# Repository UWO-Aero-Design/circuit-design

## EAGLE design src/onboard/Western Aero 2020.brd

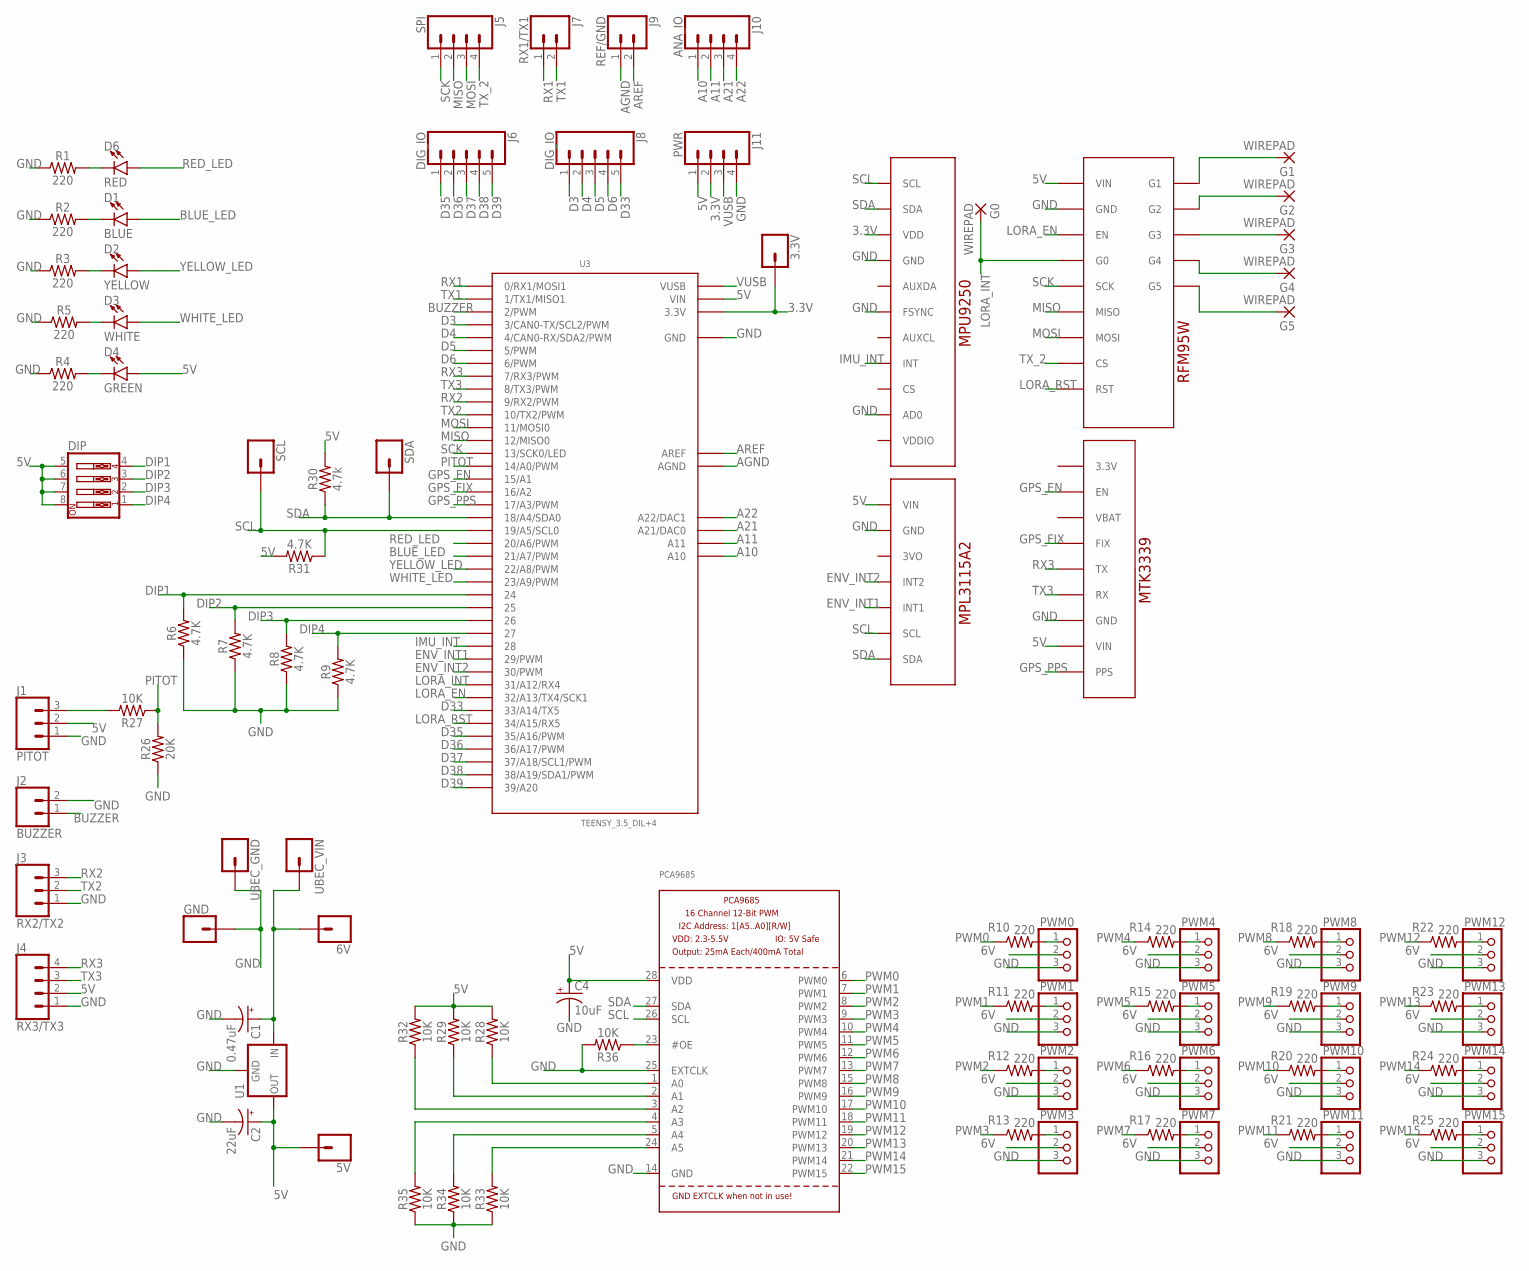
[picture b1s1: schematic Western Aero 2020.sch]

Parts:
3.3V, 5V, 6V: CONN_01; 1X01
C1: 0.47uF; CPOL-RADIAL-2.5MM-5MM
C2: 22uF; CPOL-RADIAL-2.5MM-5MM
C4: 10uF; CPOL-RADIAL-2.5MM-5MM
D1: BLUE; LED_5MM
D2: YELLOW; LED_5MM
D3: WHITE; LED_5MM
D4: GREEN; LED_5MM
D6: RED; LED_5MM
DIP: SW_DIP-4; EDG-04
G0, G1, G2, G3, G4, G5: WIREPAD; 2,15/1,0
GND: CONN_01; 1X01
J1: PITOT; 1X03
J2: BUZZER; 1X02
J3: RX2/TX2; 1X03
J4: RX3/TX3; 1X04
J5: SPI; 1X04
J6, J8: DIG_IO; 1X05
J7: RX1/TX1; 1X02
J9: REF/GND; 1X02
J10: ANA_IO; 1X04
J11: PWR; 1X04
JP1: PWM0; 1X03
JP2: PWM1; 1X03
JP3: PWM2; 1X03
JP4: PWM3; 1X03
JP5: PWM4; 1X03
JP6: PWM5; 1X03
JP7: PWM6; 1X03
JP8: PWM7; 1X03
JP9: PWM8; 1X03
JP10: PWM9; 1X03
JP11: PWM10; 1X03
JP12: PWM11; 1X03
JP13: PWM12; 1X03
JP14: PWM13; 1X03
JP15: PWM14; 1X03
JP16: PWM15; 1X03
PCA9685: PCA9685; TSSOP28
R1, R2, R3, R4, R5, R10, R11, R12, R13, R14, R15, R16, R17, R18, R19, R20, R21, R22, R23, R24, R25: 220; AXIAL-0.3
R6, R7, R8, R9, R31: 4.7K; AXIAL-0.3
R26: 20K; AXIAL-0.3
R27, R28, R29, R32, R33, R34, R35, R36: 10K; AXIAL-0.3
R30: 4.7k; AXIAL-0.3
SCL: CONN_01; 1X01
SDA: CONN_01; 1X01
U1: V_REG_78XXSINK; TO220-IGO
U3: TEENSY_3.5_DIL+4
U5: SPARKFUN_MPU9250_IMU
U6: ADAFRUIT_MPL3115A2_BAROMETER
U8: ADAFRUIT_RFM95W_LORA_RADIO
U9: ADAFRUIT_MTK3339_GPS
UBEC_GND: CONN_01; 1X01
UBEC_VIN: CONN_01; 1X01

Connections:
3.3V: 3.3V.1, J11.2, U3.3.3V, U3.3.3V3 (3.3V), U5.VDD
5V: 5V.1, C2.1 (+), C4.1 (+), D4.A, DIP.5, DIP.6, DIP.7, DIP.8, J1.2, J4.2, J11.1, PCA9685.28 (VDD), R28.P$2 (2), R29.P$2 (2), R30.P$2 (2), R31.P$2 (2), R32.P$2 (2), U1.OUT, U3.VIN, U6.VIN, U8.1 (VIN), U9.VIN
6V: 6V.1, C1.1 (+), JP1.2, JP2.2, JP3.2, JP4.2, JP5.2, JP6.2, JP7.2, JP8.2, JP9.2, JP10.2, JP11.2, JP12.2, JP13.2, JP14.2, JP15.2, JP16.2, U1.IN, UBEC_VIN.1
A10: J10.1, U3.A10
A11: J10.2, U3.A11
A21: J10.3, U3.A21 (A21/DAC0)
A22: J10.4, U3.A22 (A22/DAC1)
AGND: J9.1, U3.AGND
AREF: J9.2, U3.AREF
BLUE_LED: D1.A, U3.21/A7 (21/A7/PWM)
BUZZER: J2.1, U3.2 (2/PWM)
D3: J8.1, U3.3 (3/CAN0-TX/SCL2/PWM)
D4: J8.2, U3.4 (4/CAN0-RX/SDA2/PWM)
D5: J8.3, U3.5 (5/PWM)
D6: J8.4, U3.6 (6/PWM)
D33: J8.5, U3.33/A14 (33/A14/TX5)
D35: J6.1, U3.35/A16 (35/A16/PWM)
D36: J6.2, U3.36/A17 (36/A17/PWM)
D37: J6.3, U3.37/A18 (37/A18/SCL1/PWM)
D38: J6.4, U3.38/A19 (38/A19/SDA1/PWM)
D39: J6.5, U3.39/A20
DIP1: DIP.4, R6.P$2 (2), U3.24
DIP2: DIP.3, R7.P$2 (2), U3.25
DIP3: DIP.2, R8.P$2 (2), U3.26
DIP4: DIP.1, R9.P$2 (2), U3.27
ENV_INT1: U3.29 (29/PWM), U6.INT1
ENV_INT2: U3.30 (30/PWM), U6.INT2
GND: C1.2 (-), C2.2 (-), C4.2 (-), GND.1, J1.1, J2.2, J3.1, J4.1, J11.4, JP1.3, JP2.3, JP3.3, JP4.3, JP5.3, JP6.3, JP7.3, JP8.3, JP9.3, JP10.3, JP11.3, JP12.3, JP13.3, JP14.3, JP15.3, JP16.3, PCA9685.14 (GND), PCA9685.25 (EXTCLK), R1.P$1 (1), R2.P$1 (1), R3.P$1 (1), R4.P$1 (1), R5.P$1 (1), R6.P$1 (1), R7.P$1 (1), R8.P$1 (1), R9.P$1 (1), R26.P$1 (1), R33.P$1 (1), R34.P$1 (1), R35.P$1 (1), R36.P$2 (2), U1.GND, U3.GND, U3.GND1 (GND), U5.AD0, U5.FSYNC, U5.GND, U6.GND, U8.2 (GND), U9.GND, UBEC_GND.1
GPS_EN: U3.15/A1, U9.EN
GPS_FIX: U3.16/A2, U9.FIX
GPS_PPS: U3.17/A3 (17/A3/PWM), U9.PPS
IMU_INT: U3.28, U5.INT
LORA_EN: U3.32/A13 (32/A13/TX4/SCK1), U8.3 (EN)
LORA_INT: G0.1, U3.31/A12 (31/A12/RX4), U8.4 (G0)
LORA_RST: U3.34/A15 (34/A15/RX5), U8.9 (RST)
MISO: J5.2, U3.12 (12/MISO0), U8.6 (MISO)
MOSI: J5.3, U3.11 (11/MOSI0), U8.7 (MOSI)
unnamed: JP1.1, R10.P$2 (2)
unnamed: D6.K (C), R1.P$2 (2)
unnamed: D1.K (C), R2.P$2 (2)
unnamed: D2.K (C), R3.P$2 (2)
unnamed: D3.K (C), R5.P$2 (2)
unnamed: D4.K (C), R4.P$2 (2)
unnamed: G5.1, U8.14 (G5)
unnamed: G1.1, U8.10 (G1)
unnamed: JP2.1, R11.P$2 (2)
unnamed: G2.1, U8.11 (G2)
unnamed: JP3.1, R12.P$2 (2)
unnamed: JP4.1, R13.P$2 (2)
unnamed: JP5.1, R14.P$2 (2)
unnamed: JP6.1, R15.P$2 (2)
unnamed: JP7.1, R16.P$2 (2)
unnamed: JP8.1, R17.P$2 (2)
unnamed: JP9.1, R18.P$2 (2)
unnamed: JP10.1, R19.P$2 (2)
unnamed: JP11.1, R20.P$2 (2)
unnamed: JP12.1, R21.P$2 (2)
unnamed: JP13.1, R22.P$2 (2)
unnamed: JP14.1, R23.P$2 (2)
unnamed: JP15.1, R24.P$2 (2)
unnamed: JP16.1, R25.P$2 (2)
unnamed: G4.1, U8.13 (G4)
unnamed: G3.1, U8.12 (G3)
unnamed: PCA9685.1 (A0), R28.P$1 (1)
unnamed: J1.3, R27.P$2 (2)
unnamed: PCA9685.24 (A5), R33.P$2 (2)
unnamed: PCA9685.23 (#OE), R36.P$1 (1)
unnamed: PCA9685.5 (A4), R34.P$2 (2)
unnamed: PCA9685.4 (A3), R35.P$2 (2)
unnamed: PCA9685.3 (A2), R32.P$1 (1)
unnamed: PCA9685.2 (A1), R29.P$1 (1)
PITOT: R26.P$2 (2), R27.P$1 (1), U3.14/A0 (14/A0/PWM)
PWM0: PCA9685.6 (PWM0), R10.P$1 (1)
PWM1: PCA9685.7 (PWM1), R11.P$1 (1)
PWM2: PCA9685.8 (PWM2), R12.P$1 (1)
PWM3: PCA9685.9 (PWM3), R13.P$1 (1)
PWM4: PCA9685.10 (PWM4), R14.P$1 (1)
PWM5: PCA9685.11 (PWM5), R15.P$1 (1)
PWM6: PCA9685.12 (PWM6), R16.P$1 (1)
PWM7: PCA9685.13 (PWM7), R17.P$1 (1)
PWM8: PCA9685.15 (PWM8), R18.P$1 (1)
PWM9: PCA9685.16 (PWM9), R19.P$1 (1)
PWM10: PCA9685.17 (PWM10), R20.P$1 (1)
PWM11: PCA9685.18 (PWM11), R21.P$1 (1)
PWM12: PCA9685.19 (PWM12), R22.P$1 (1)
PWM13: PCA9685.20 (PWM13), R23.P$1 (1)
PWM14: PCA9685.21 (PWM14), R24.P$1 (1)
PWM15: PCA9685.22 (PWM15), R25.P$1 (1)
RED_LED: D6.A, U3.20/A6 (20/A6/PWM)
RX1: J7.1, U3.0 (0/RX1/MOSI1)
RX2: J3.3, U3.9 (9/RX2/PWM)
RX3: J4.4, U3.7 (7/RX3/PWM), U9.TX
SCK: J5.1, U3.13 (13/SCK0/LED), U8.5 (SCK)
SCL: PCA9685.26 (SCL), R31.P$1 (1), SCL.1, U3.19/A5 (19/A5/SCL0), U5.SCL, U6.SCL
SDA: PCA9685.27 (SDA), R30.P$1 (1), SDA.1, U3.18/A4 (18/A4/SDA0), U5.SDA, U6.SDA
TX1: J7.2, U3.1 (1/TX1/MISO1)
TX2: J3.2, U3.10 (10/TX2/PWM)
TX3: J4.3, U3.8 (8/TX3/PWM), U9.RX
TX_2: J5.4, U8.8 (CS)
VUSB: J11.3, U3.VUSB
WHITE_LED: D3.A, U3.23/A9 (23/A9/PWM)
YELLOW_LED: D2.A, U3.22/A8 (22/A8/PWM)

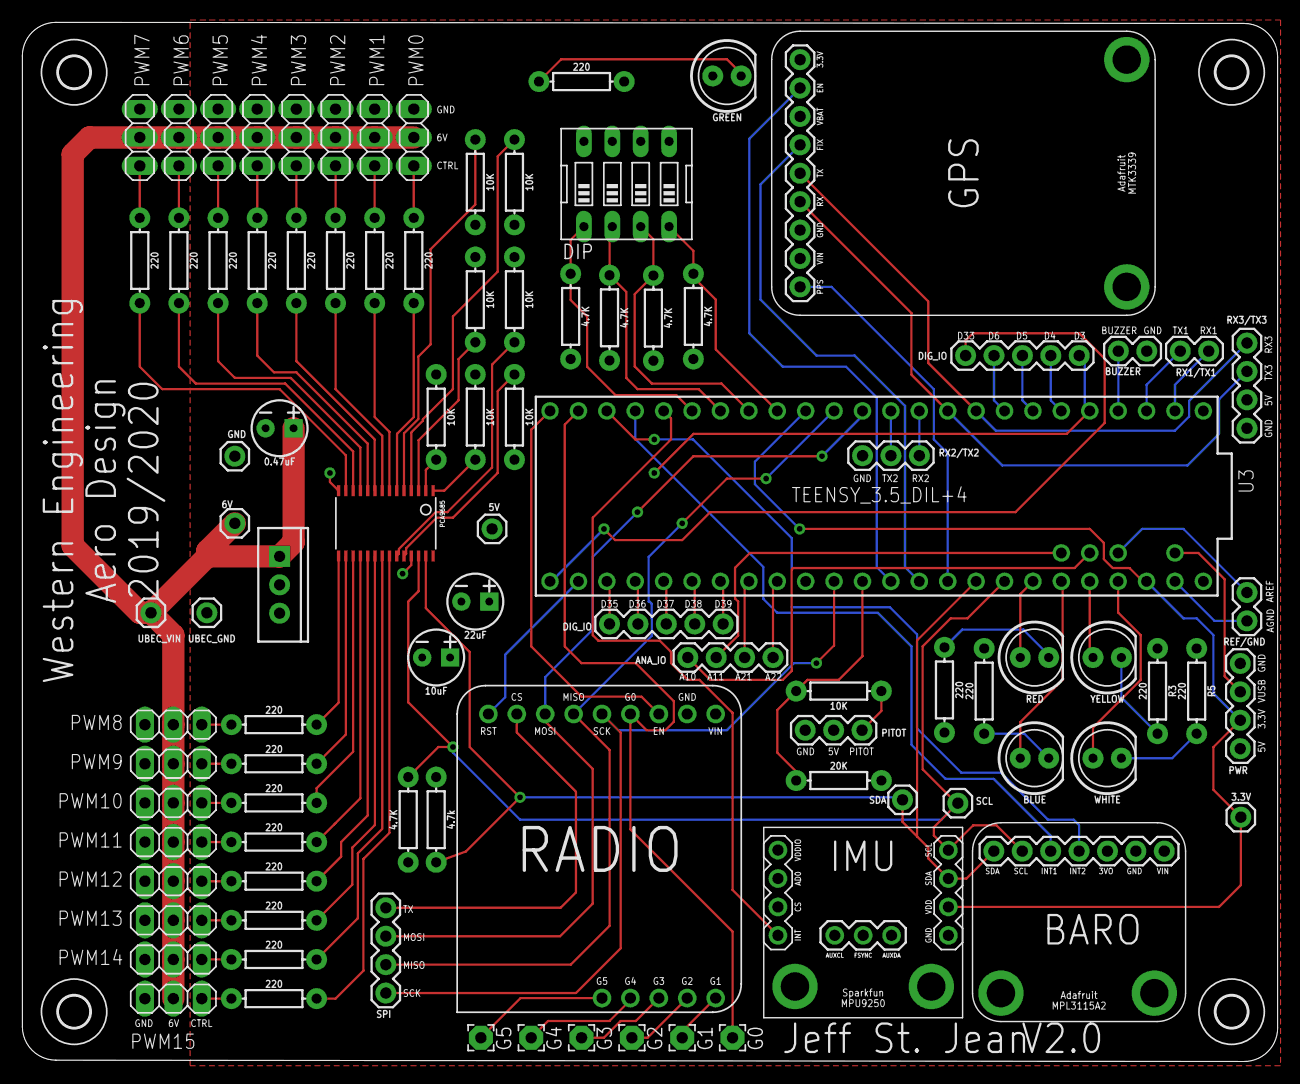
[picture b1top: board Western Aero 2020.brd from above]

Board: 2 copper layers, 112.2 x 92.9 mm, 97 parts (0 on the bottom side), 102 nets.

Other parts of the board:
H1, H2, H3, H4: MOUNT-HOLE2.8; 2,8

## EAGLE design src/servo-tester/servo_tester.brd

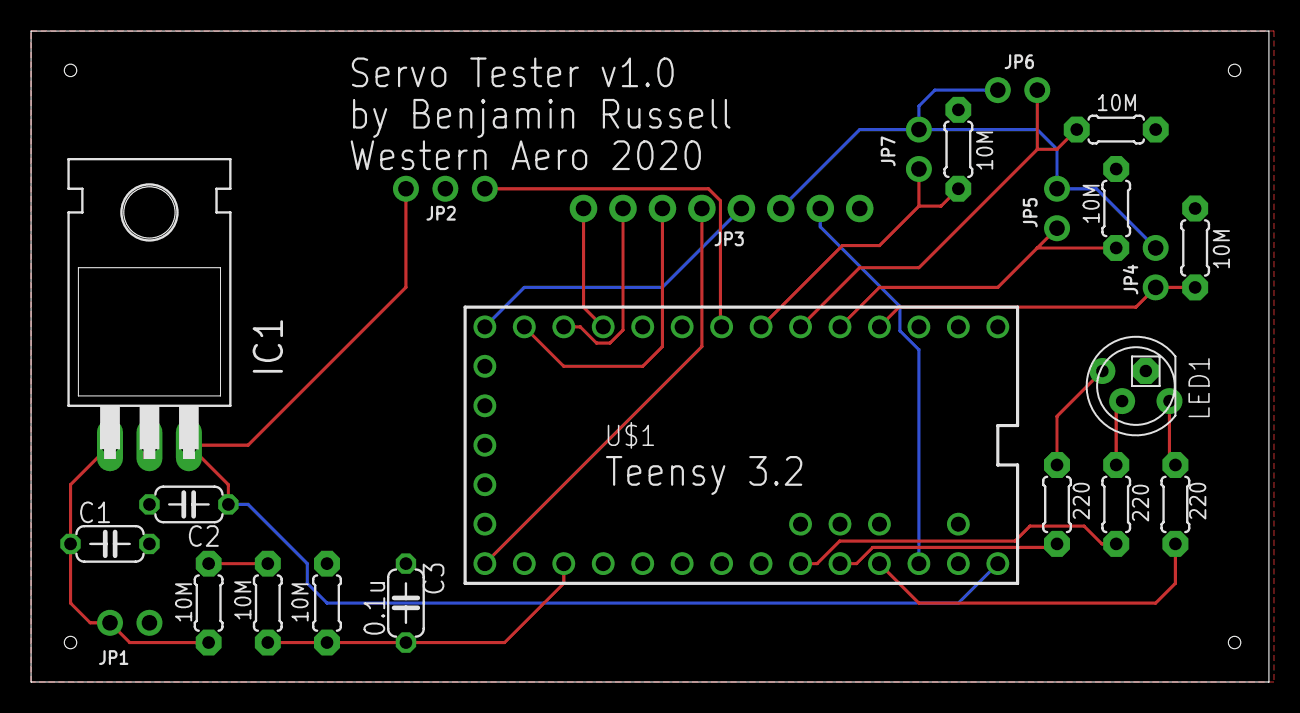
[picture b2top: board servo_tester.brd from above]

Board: 2 copper layers, 79.7 x 41.9 mm, 23 parts (0 on the bottom side), 23 nets.

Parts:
C1, C2: C050-024X044
C3: 0.1u; C050-024X044
IC1: 7806T; TO220H
JP1, JP4, JP5, JP6, JP7: 1X02_ROUND
JP2: 1X03_ROUND
JP3: 1X08_ROUND_70
LED1: RGBLED_CA-5MM; LED5MMRGB
R1, R2, R3, R7, R8, R9, R10: 10M; 0204/5
R4, R5, R6: 220; 0204/5
U$1: TEENSY_3.1-3.2_ALL_PINS; TEENSY_3.0-3.2&LC_ALL_PINS

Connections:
6V: C2.1, IC1.3, JP2.1, U$1.VIN
33V: JP3.7, U$1.3.3V, U$1.3.3V1
33V_PULLUP: JP3.6, JP4.2, JP5.2, JP6.2, JP7.2
BAT_TEST: C3.1, R2.1, R3.2, U$1.15/A1
BTN1: JP4.1, R7.1, U$1.2
BTN2: JP5.1, R8.2, U$1.3
BTN3: JP6.1, R9.2, U$1.4
BTN4: JP7.1, R10.2, U$1.5
GND: C1.2, C2.2, C3.2, IC1.2, JP1.1, JP2.2, JP3.8, LED1.2, R3.1, R7.2, R8.1, R9.1, R10.1, U$1.GND, U$1.GND1
LEDB: R4.2, U$1.22/A8
LEDG: R5.2, U$1.21/A7
LEDR: R6.2, U$1.23/A9
unnamed: LED1.1, R6.1
unnamed: LED1.4, R4.1
unnamed: LED1.3, R5.1
unnamed: R1.1, R2.2
SCREEN_CLK: JP3.2, U$1.10
SCREEN_CS: JP3.5, U$1.12
SCREEN_DATA: JP3.1, U$1.9
SCREEN_DC: JP3.3, U$1.11
SCREEN_RST: JP3.4, U$1.13
SERVO: JP2.3, U$1.6
VIN: C1.1, IC1.1, JP1.2, R1.2

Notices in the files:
parts and their libraries:
SparkFun-Connectors: Licensing: Creative Commons ShareAlike 4.0 International - https://creativecommons.org/licenses/by-sa/4.0
microbuilder: This work is placed in the public domain, and may be freely used for commercial and non-commercial work with the following conditions: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
